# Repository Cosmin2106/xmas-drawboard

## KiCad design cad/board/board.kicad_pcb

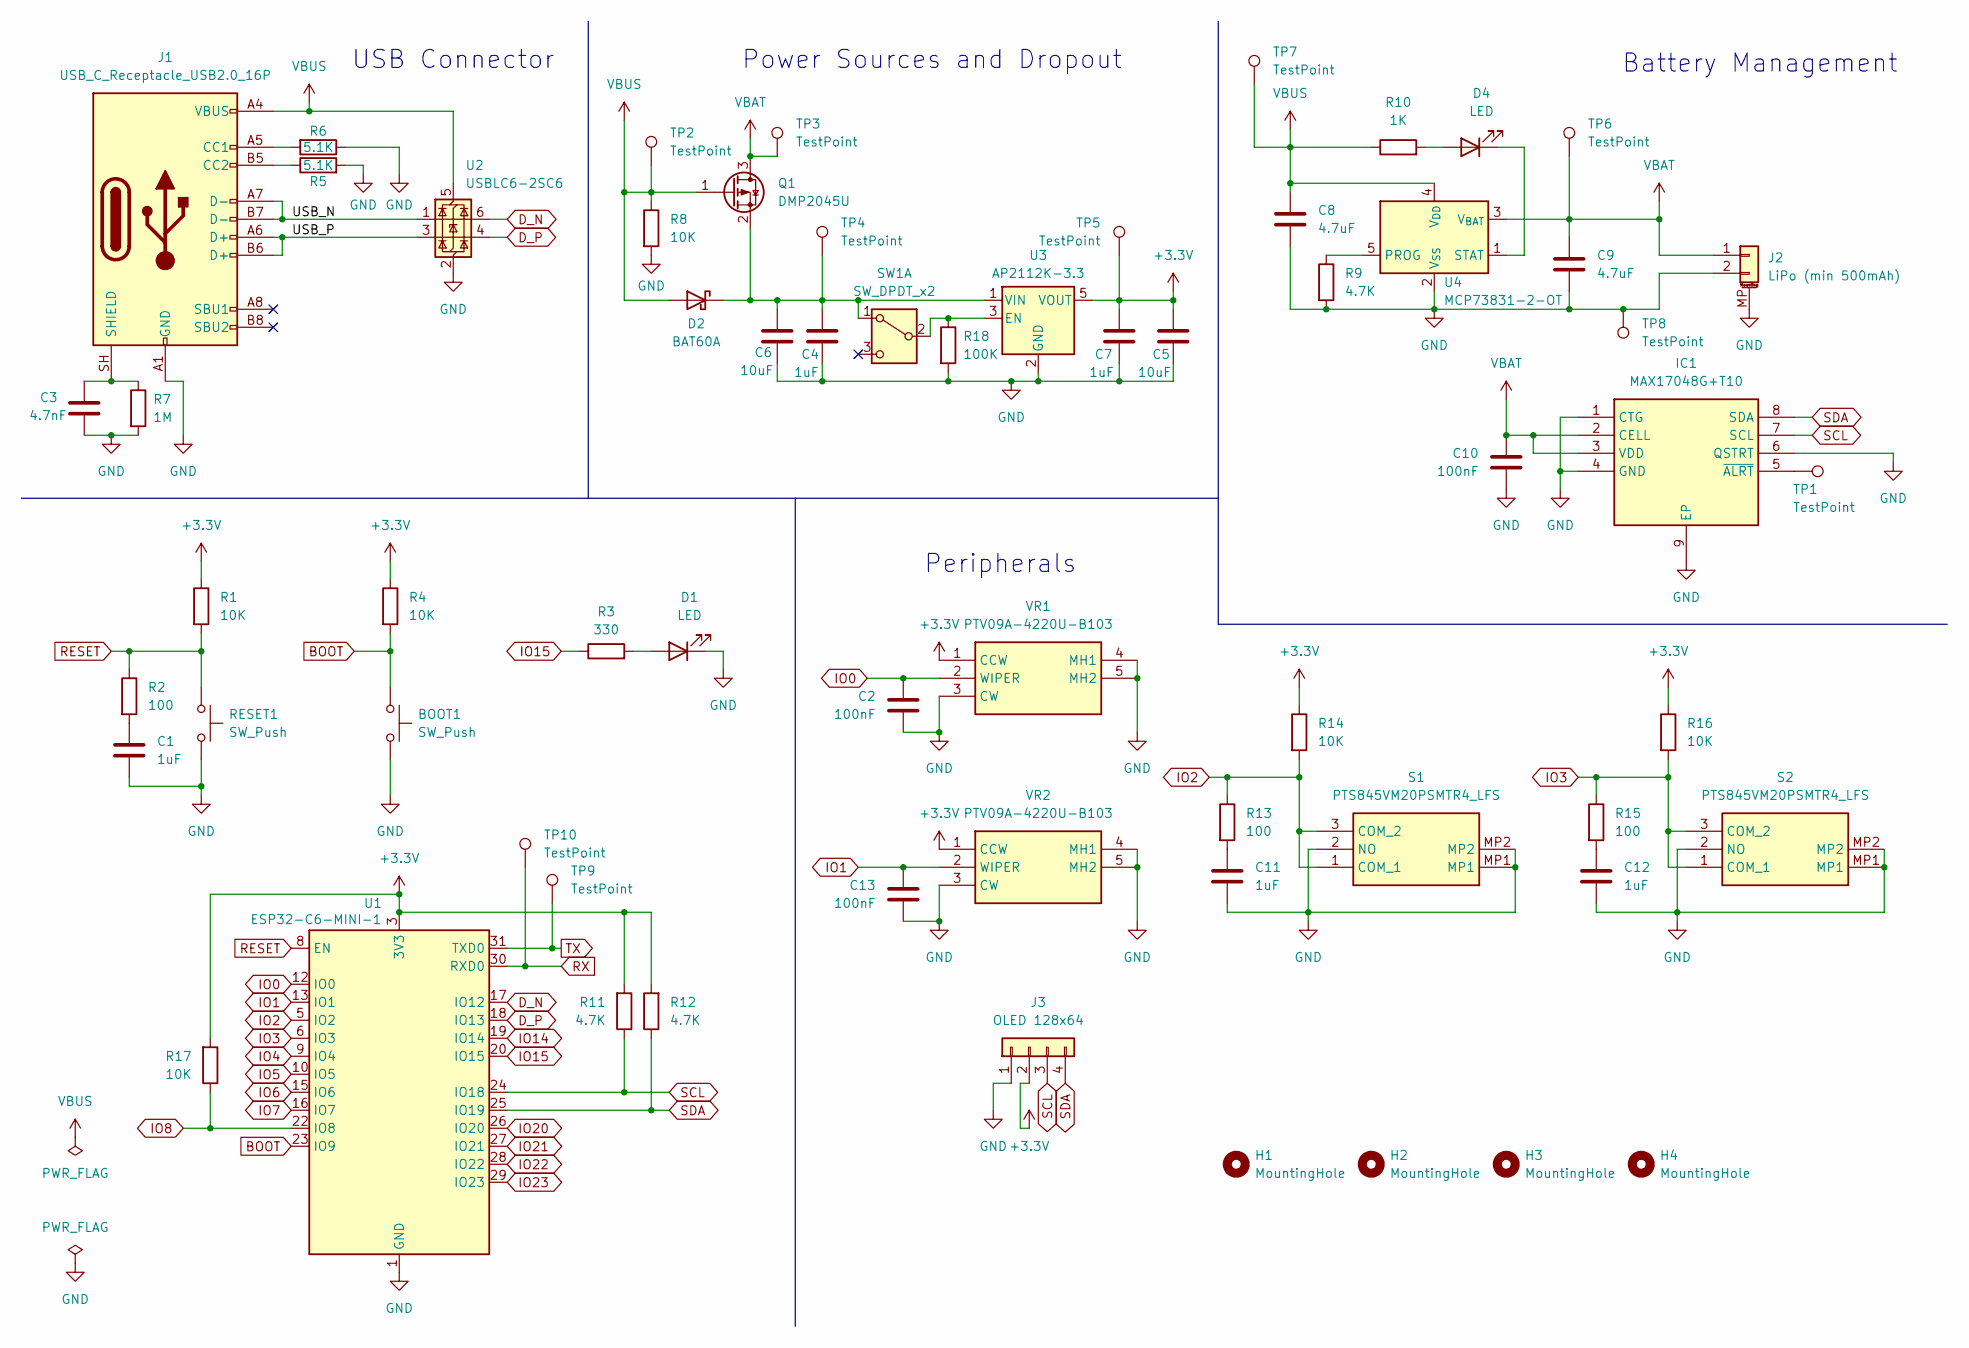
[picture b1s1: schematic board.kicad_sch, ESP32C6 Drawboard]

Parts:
BOOT1: SW_Push; SW_Push_1P1T_NO_CK_KMR2
C1, C4, C7, C11, C12: 1uF; C_0603_1608Metric
C2, C10, C13: 100nF; C_0603_1608Metric
C3: 4.7nF; C_0603_1608Metric
C5, C6: 10uF; C_0603_1608Metric
C8, C9: 4.7uF; C_0603_1608Metric
D1, D4: LED; LED_0603_1608Metric
D2: BAT60A; D_SOD-323
H1, H2, H3, H4: MountingHole; RPi_Mounting_Hole
IC1: MAX17048G+T10; SON50P200X200X80-9N-D; Mouser Part Number 700-MAX17048G+T10
J1: USB_C_Receptacle_USB2.0_16P; USB_C_Receptacle_GCT_USB4105-xx-A_16P_TopMnt_Horizontal
J2: LiPo (min 500mAh); JST_PH_S2B-PH-SM4-TB_1x02-1MP_P2.00mm_Horizontal
J3: OLED 128x64; OLED_128x64_I2C_BOARD
Q1: DMP2045U; TSOT-23
R1, R4, R8, R14, R16, R17: 10K; R_0603_1608Metric
R2, R13, R15: 100; R_0603_1608Metric
R3: 330; R_0603_1608Metric
R5, R6: 5.1K; R_0603_1608Metric
R7: 1M; R_0603_1608Metric
R9, R11, R12: 4.7K; R_0603_1608Metric
R10: 1K; R_0603_1608Metric
R18: 100K; R_0603_1608Metric
RESET1: SW_Push; SW_Push_1P1T_NO_CK_KMR2
S1, S2: PTS845VM20PSMTR4_LFS; PTS845VM20PSMTR4LFS; Manufacturer_Part_Number PTS845VM20PSMTR4 LFS
SW1: SW_DPDT_x2; SW_SPDT_CK_JS102011SAQN
TP1, TP2, TP3, TP4, TP5, TP6, TP7, TP8, TP9, TP10: TestPoint; TestPoint_Pad_D1.5mm
U1: ESP32-C6-MINI-1
U2: USBLC6-2SC6; SOT-23-6
U3: AP2112K-3.3; SOT-23-5
U4: MCP73831-2-OT; SOT-23-5
VR1, VR2: PTV09A-4220U-B103; PTV09A4220FB103; Mouser Part Number 652-PTV09A-4220FB103

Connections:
+3.3V: C5.1, C7.1, J3.2, R1.1, R4.1, R11.2, R12.2, R14.1, R16.1, R17.2, TP5.1 (1_1), U1.3 (3V3), U3.5 (VOUT), VR1.1 (CCW), VR2.1 (CCW)
/USB_N: J1.A7 (D-), J1.B7 (D-), U2.1 (I/O1)
/USB_P: J1.A6 (D+), J1.B6 (D+), U2.3 (I/O2)
BOOT: BOOT1.1, R4.2, U1.23 (IO9)
D_N: U1.17 (IO12), U2.6 (I/O1)
D_P: U1.18 (IO13), U2.4 (I/O2)
GND: BOOT1.2, C1.2, C2.2, C3.2, C4.2, C5.2, C6.2, C7.2, C8.1, C9.1, C10.2, C11.2, C12.2, C13.2, D1.1 (K), IC1.1 (CTG), IC1.4 (GND), IC1.6 (QSTRT), IC1.9 (EP), J1.A1 (GND), J1.A12 (GND), J1.B1 (GND), J1.B12 (GND), J2.2, J2.MP (MountPin), J3.1, R5.2, R6.1, R7.2, R8.2, R9.2, R18.2, RESET1.2, S1.2 (NO), S1.MP1, S1.MP2, S2.2 (NO), S2.MP1, S2.MP2, TP8.1 (1_1), U1.1 (GND), U1.2 (GND), U1.11 (GND), U1.14 (GND), U1.36 (GND), U1.37 (GND), U1.38 (GND), U1.39 (GND), U1.40 (GND), U1.41 (GND), U1.42 (GND), U1.43 (GND), U1.44 (GND), U1.45 (GND), U1.46 (GND), U1.47 (GND), U1.48 (GND), U1.49 (GND), U1.50 (GND), U1.51 (GND), U1.52 (GND), U1.53 (GND), U2.2 (GND), U3.2 (GND), U4.2 (V_{SS}), VR1.3 (CW), VR1.4 (MH1), VR1.5 (MH2), VR2.3 (CW), VR2.4 (MH1), VR2.5 (MH2)
IO0: C2.1, U1.12 (IO0), VR1.2 (WIPER)
IO1: C13.1, U1.13 (IO1), VR2.2 (WIPER)
IO2: R13.1, R14.2, S1.1 (COM_1), S1.3 (COM_2), U1.5 (IO2)
IO3: R15.1, R16.2, S2.1 (COM_1), S2.3 (COM_2), U1.6 (IO3)
IO4: U1.9 (IO4)
IO5: U1.10 (IO5)
IO6: U1.15 (IO6)
IO7: U1.16 (IO7)
IO8: R17.1, U1.22 (IO8)
IO14: U1.19 (IO14)
IO15: R3.1, U1.20 (IO15)
IO20: U1.26 (IO20)
IO21: U1.27 (IO21)
IO22: U1.28 (IO22)
IO23: U1.29 (IO23)
unnamed: C1.1, R2.2
unnamed: C11.1, R13.2
unnamed: C12.1, R15.2
unnamed: D1.2 (A), R3.2
unnamed: C4.1, C6.1, D2.1 (K), Q1.2 (S), SW1.1 (A), TP4.1 (1_1), U3.1 (VIN)
unnamed: D4.2 (A), R10.2
unnamed: D4.1 (K), U4.1 (STAT)
unnamed: IC1.5 (~ALRT), TP1.1 (1_1)
unnamed: J1.A5 (CC1), R6.2
unnamed: J1.B5 (CC2), R5.1
unnamed: C3.1, J1.SH (SHIELD), R7.1
unnamed: R18.1, SW1.2 (B), U3.3 (EN)
unnamed: R9.1, U4.5 (PROG)
RESET: R1.2, R2.1, RESET1.1, U1.8 (EN)
RX: TP10.1 (1_1), U1.30 (RXD0)
SCL: IC1.7 (SCL), J3.3, R11.1, U1.24 (IO18)
SDA: IC1.8 (SDA), J3.4, R12.1, U1.25 (IO19)
TX: TP9.1 (1_1), U1.31 (TXD0)
VBAT: C9.2, C10.1, IC1.2 (CELL), IC1.3 (VDD), J2.1, Q1.3 (D), TP3.1 (1_1), TP6.1 (1_1), U4.3 (V_{BAT})
VBUS: C8.2, D2.2 (A), J1.A4 (VBUS), J1.A9 (VBUS), J1.B4 (VBUS), J1.B9 (VBUS), Q1.1 (G), R8.1, R10.1, TP2.1 (1_1), TP7.1 (1_1), U2.5 (VBUS), U4.4 (V_{DD})

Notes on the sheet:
USB Connector
Battery Management
Power Sources and Dropout
Peripherals

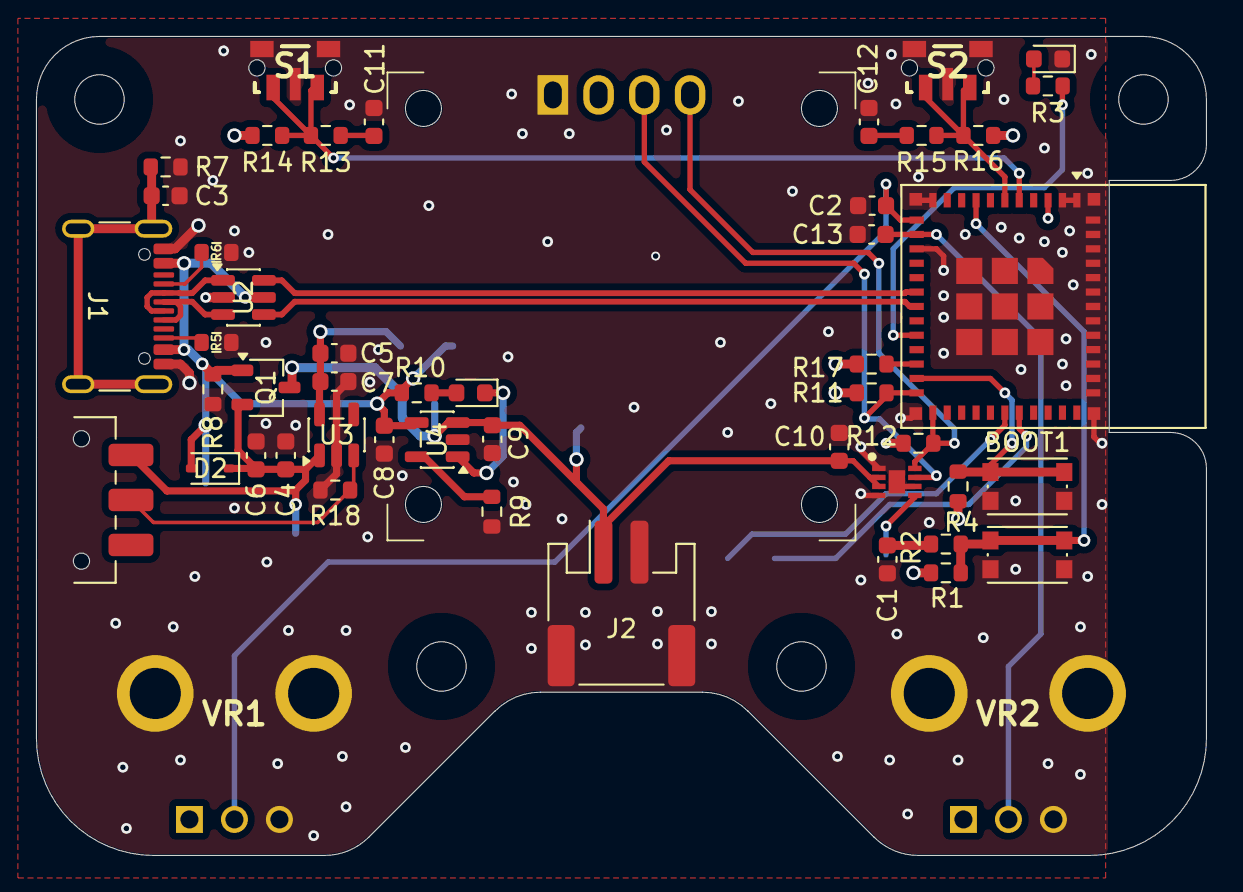
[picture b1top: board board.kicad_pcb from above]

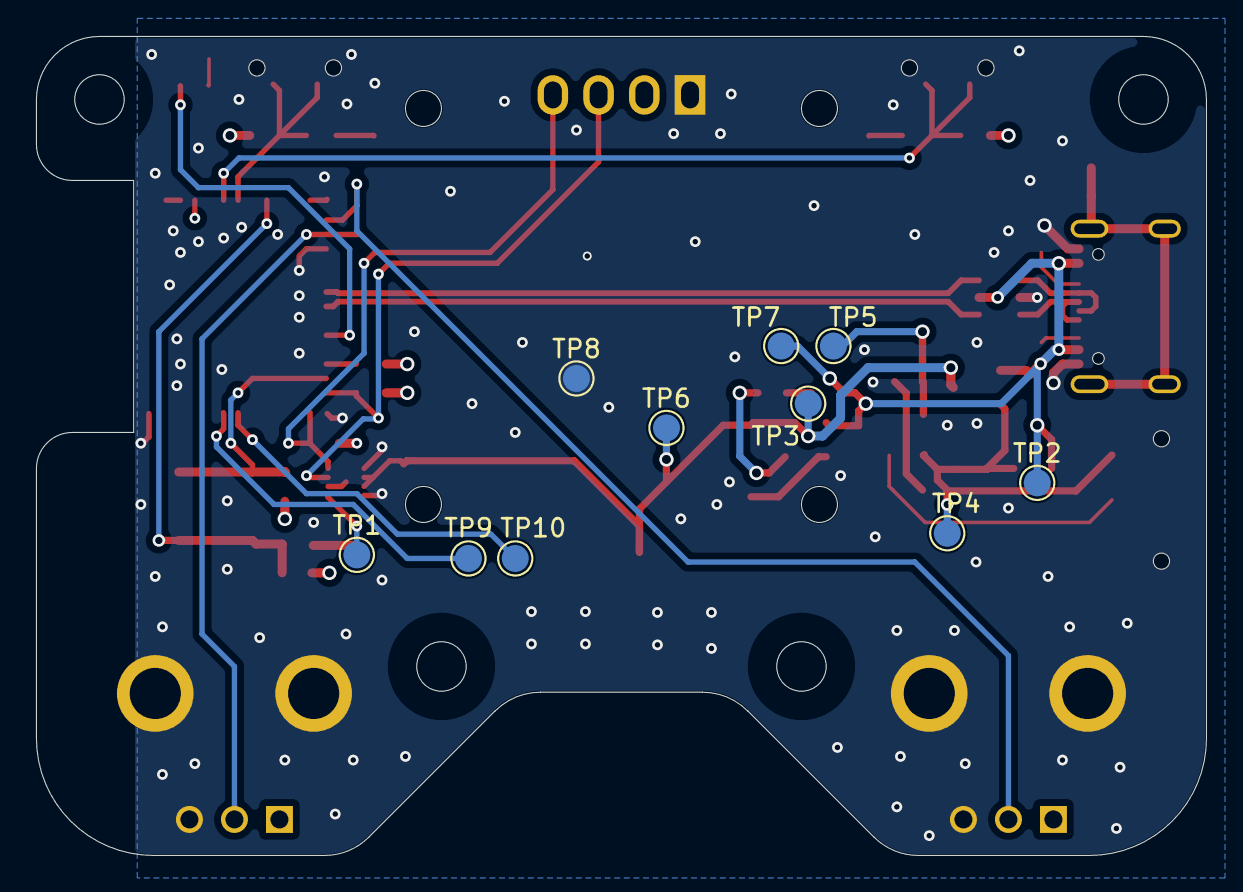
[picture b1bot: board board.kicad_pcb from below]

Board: 4 copper layers, 65.0 x 45.5 mm, 64 parts (10 on the bottom side), 33 nets.
